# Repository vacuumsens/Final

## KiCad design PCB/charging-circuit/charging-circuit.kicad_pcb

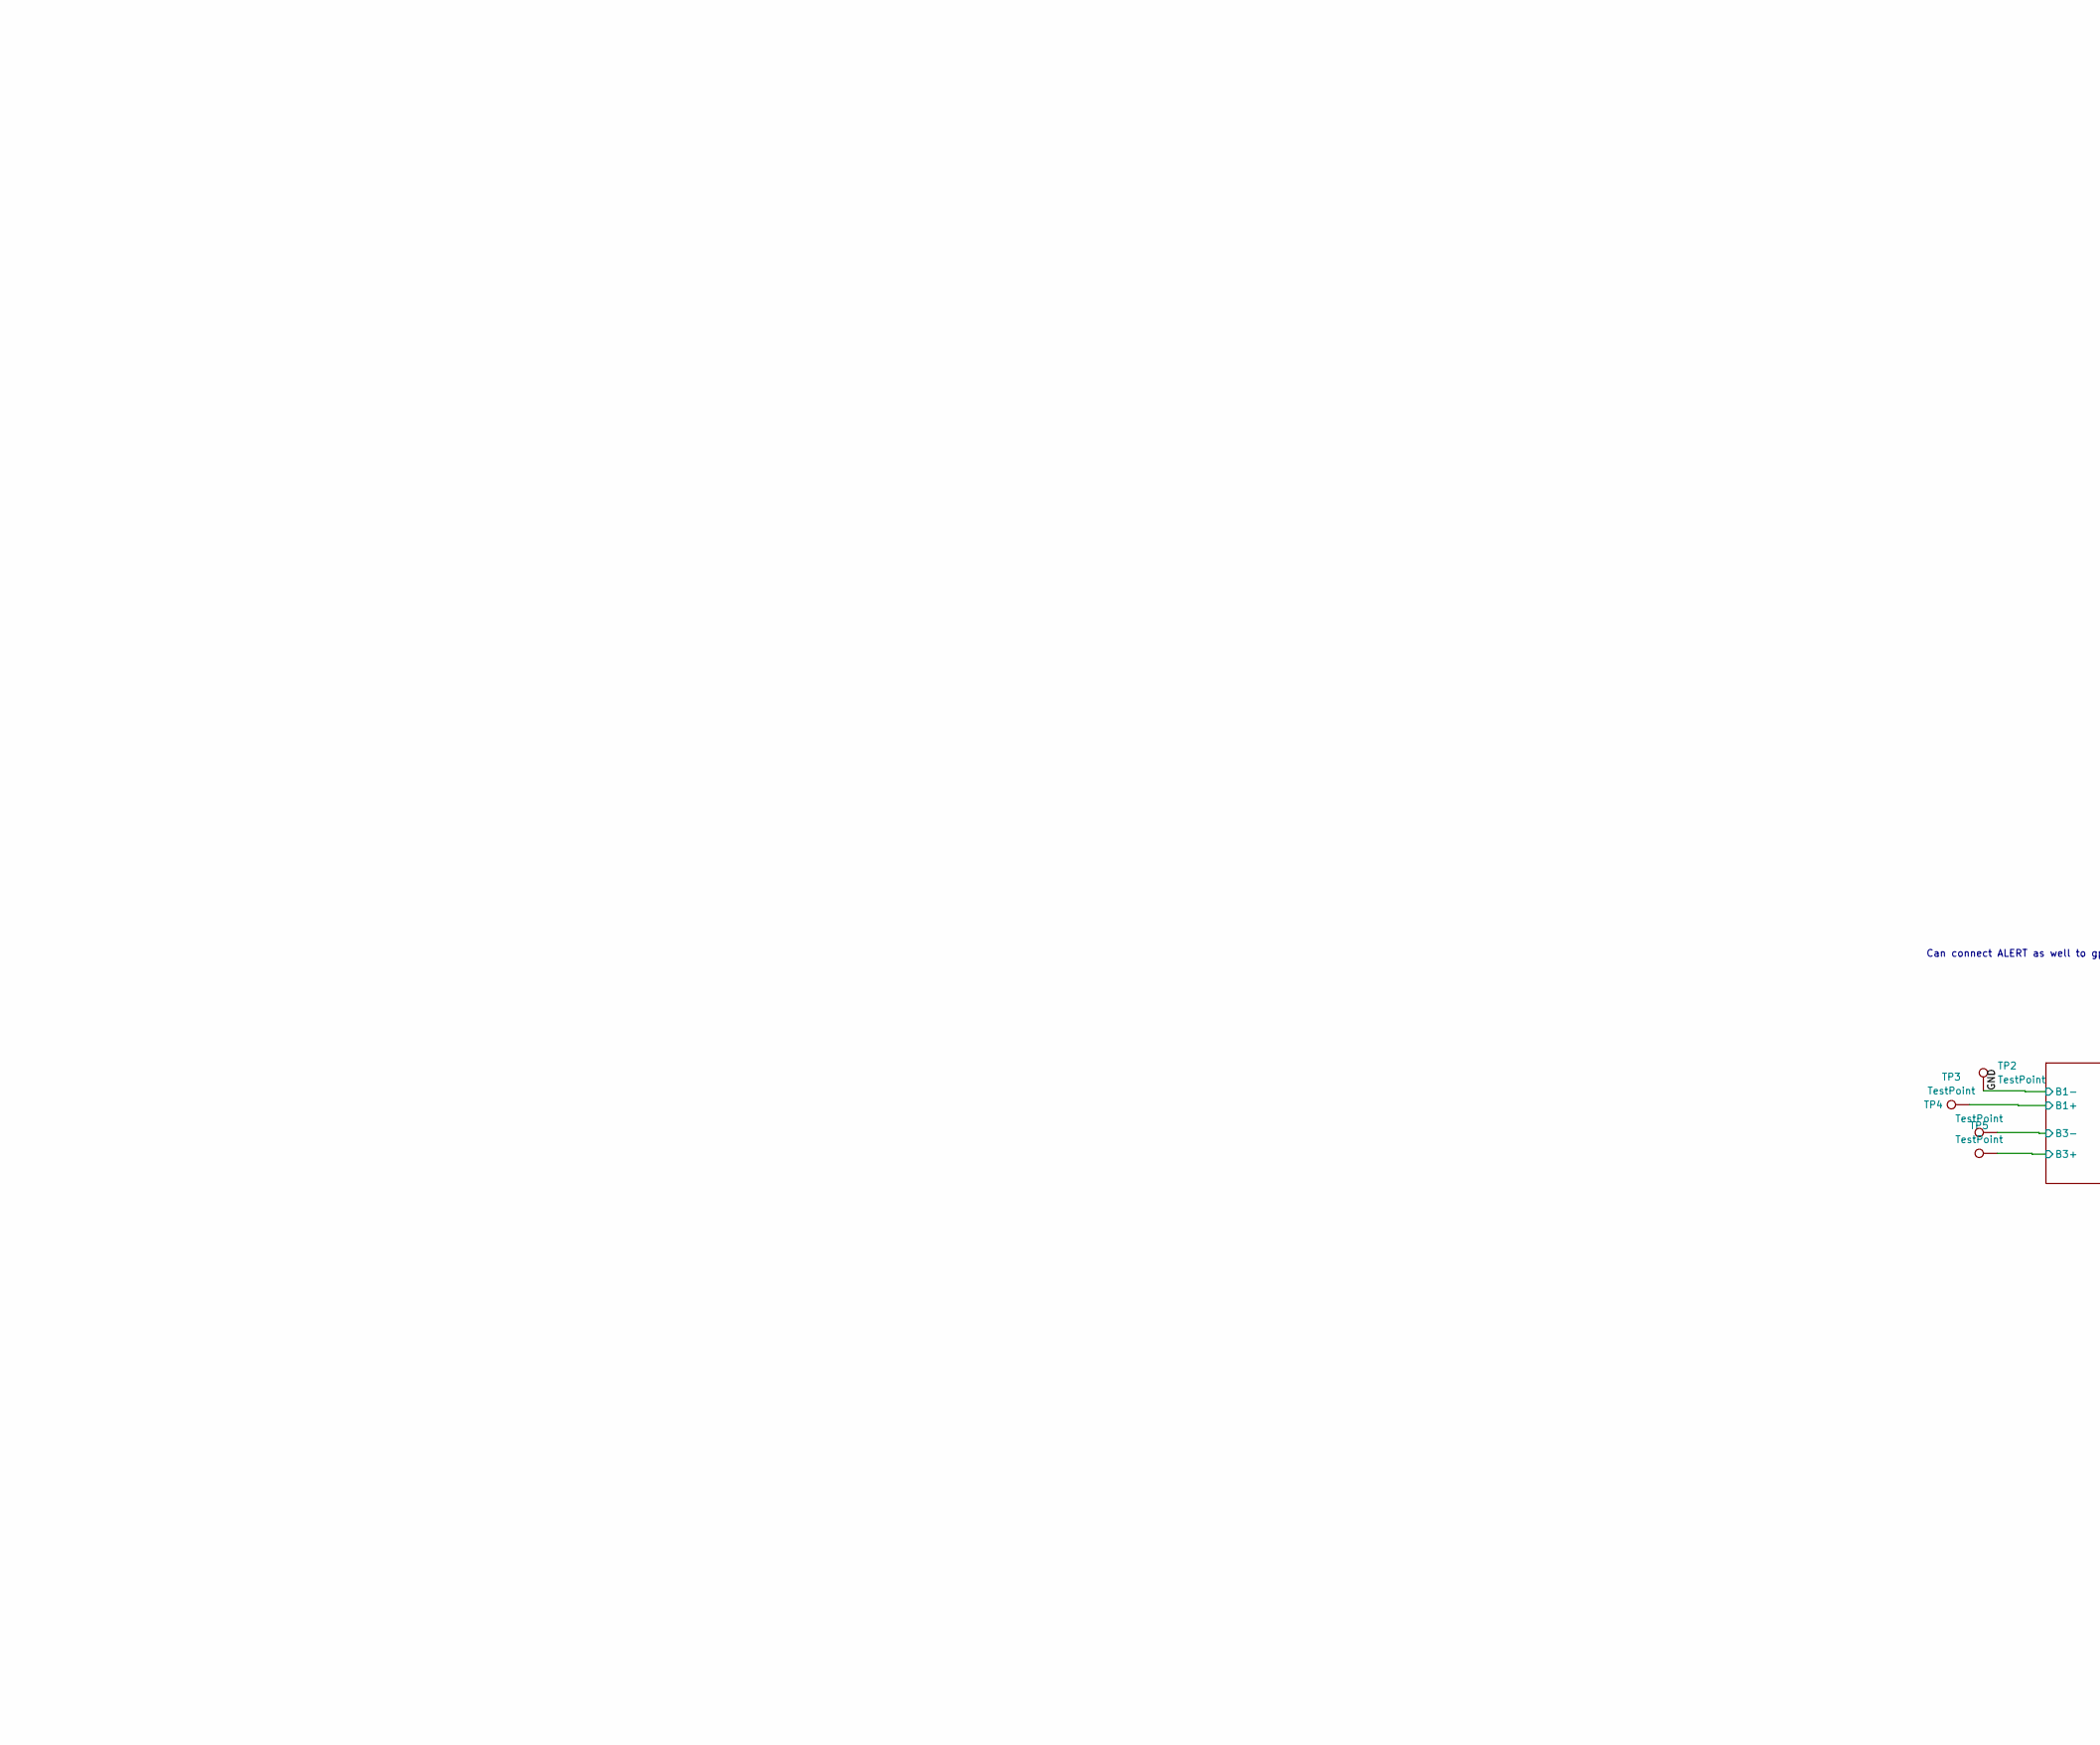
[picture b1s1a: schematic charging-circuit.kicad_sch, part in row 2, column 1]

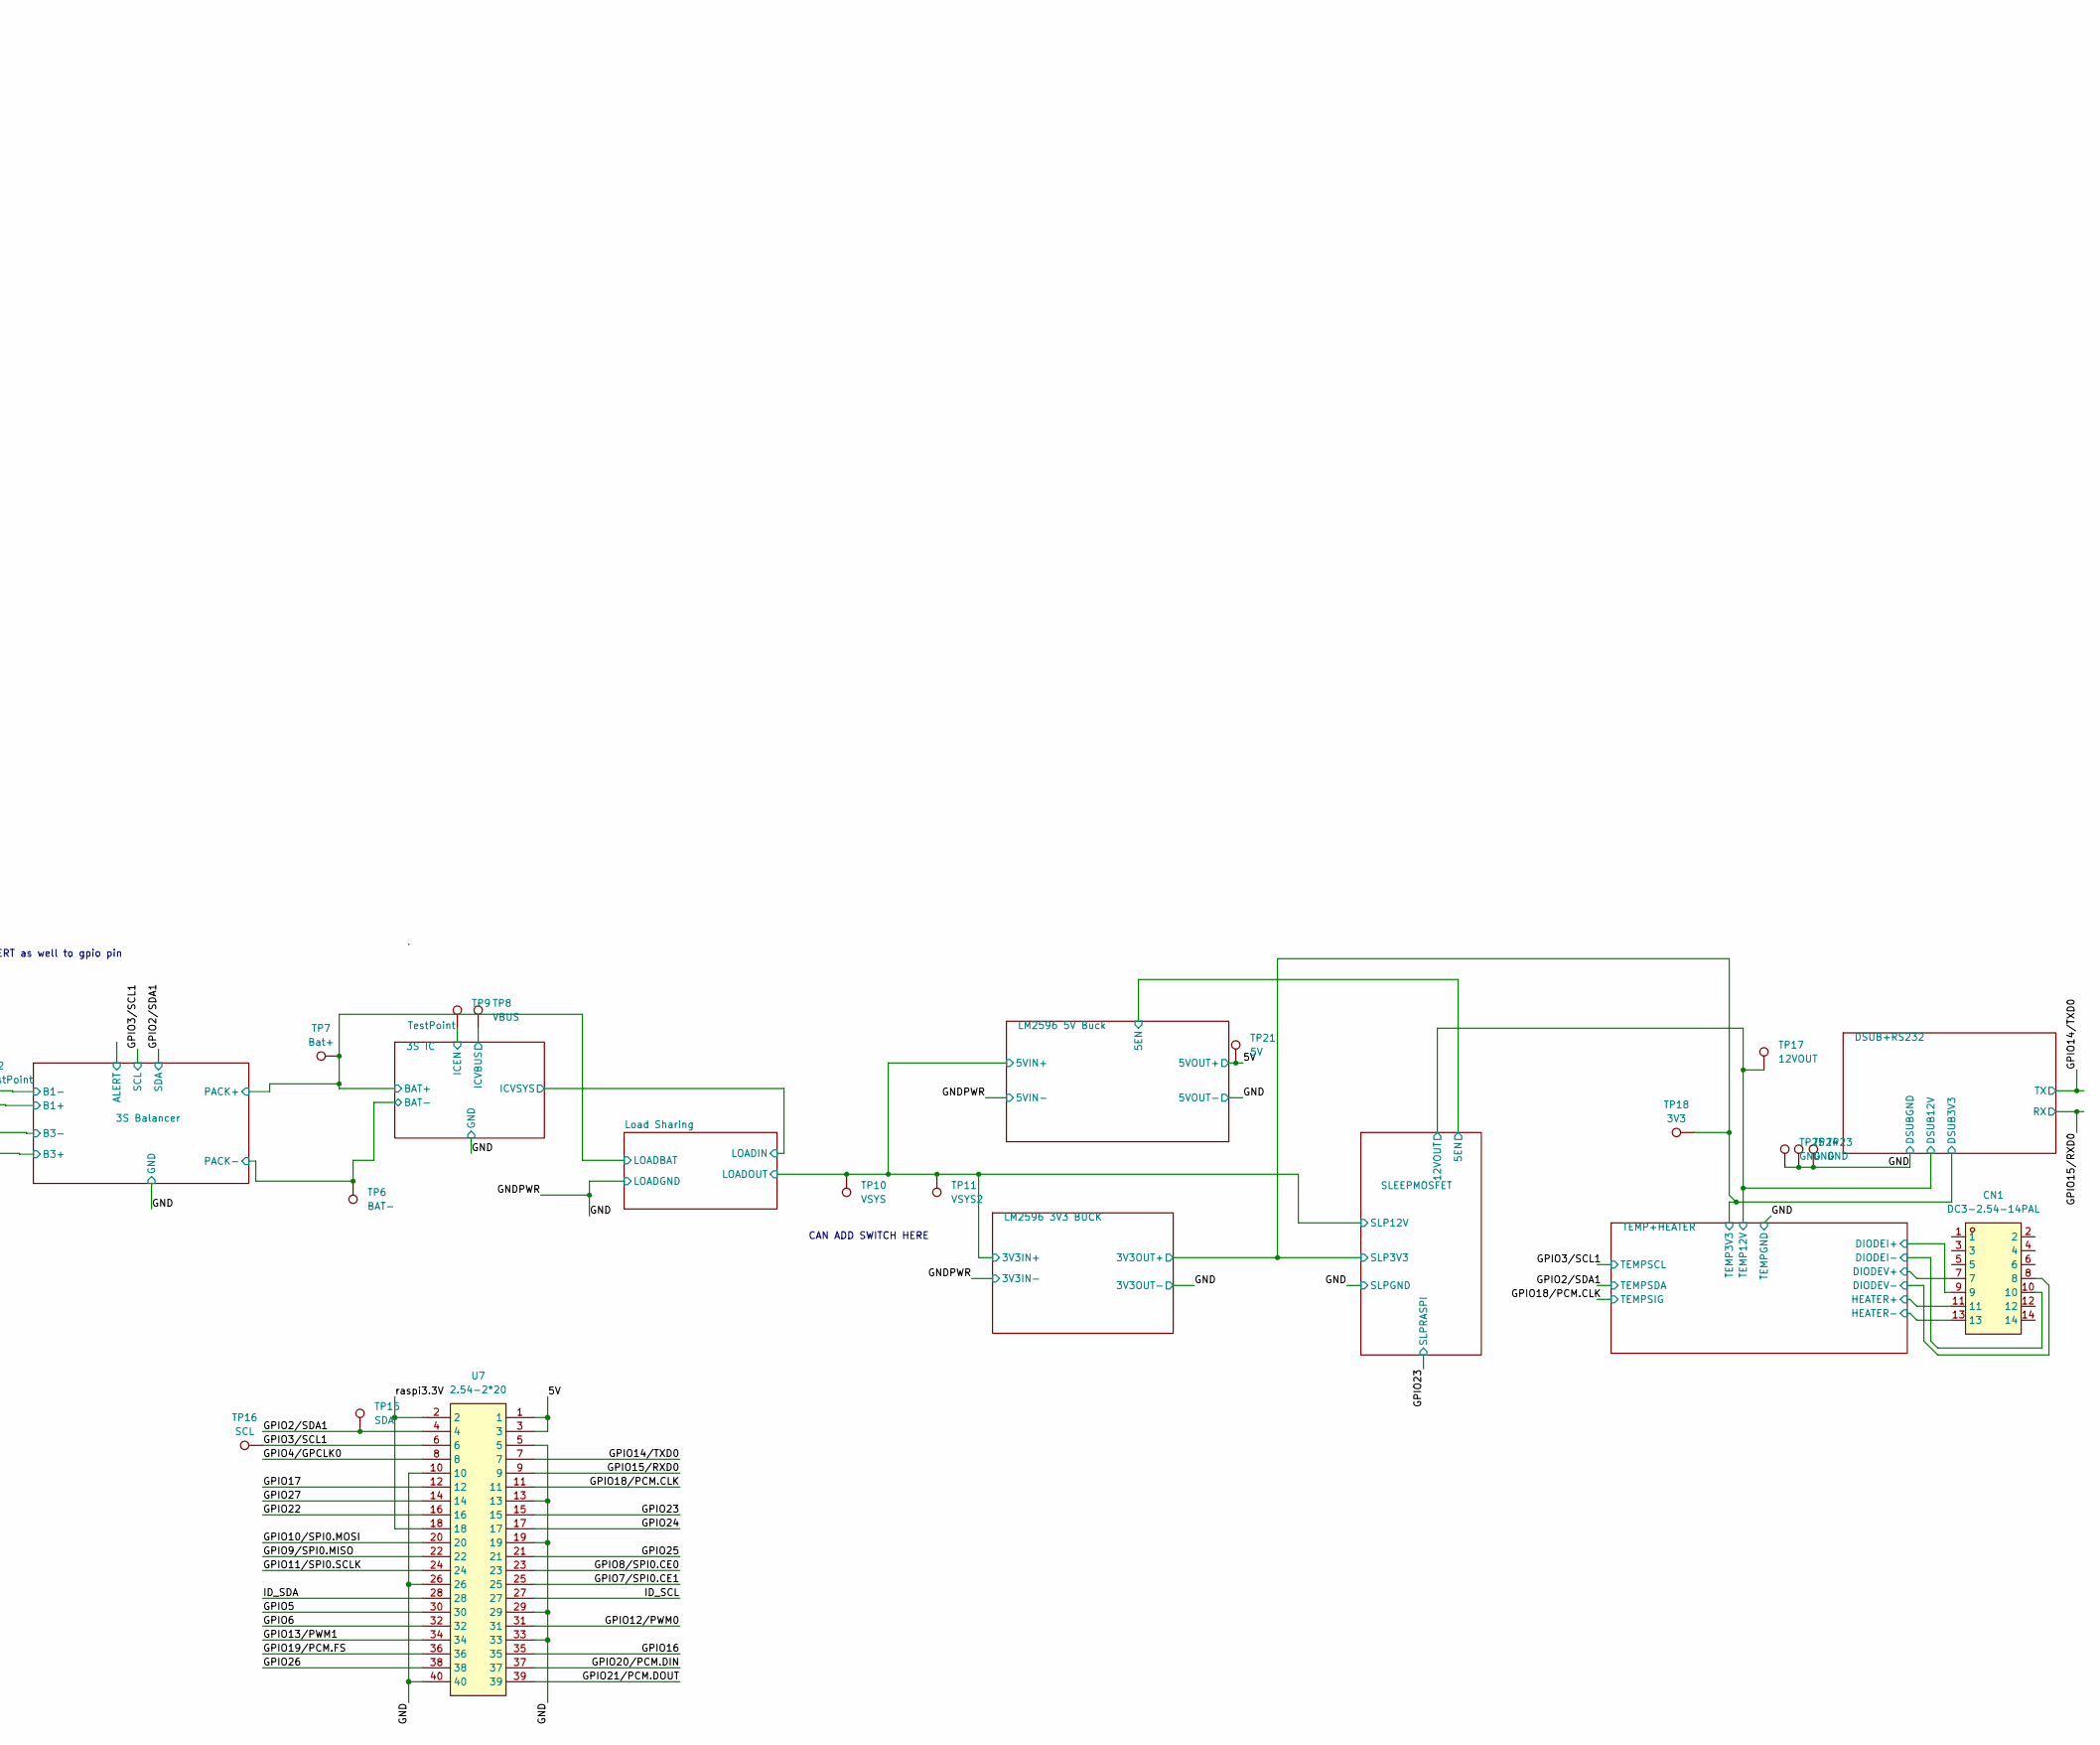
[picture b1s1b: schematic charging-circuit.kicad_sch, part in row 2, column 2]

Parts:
CN1: DC3-2.54-14PAL; IDC-TH_14P-P2.54_ZHOURI_DC3-2.54-14PAL; MPN DC3-2.54-14PAL; LCSC Part C5156673
TP2, TP3, TP4, TP5, TP9: TestPoint; PinHeader_1x01_P2.54mm_Vertical
TP6: BAT-; PinHeader_1x01_P2.54mm_Vertical
TP7: Bat+; PinHeader_1x01_P2.54mm_Vertical
TP8: VBUS; PinHeader_1x01_P2.54mm_Vertical
TP10: VSYS; PinHeader_1x01_P2.54mm_Vertical
TP11: VSYS2; PinHeader_1x01_P2.54mm_Vertical
TP15: SDA; PinHeader_1x01_P2.54mm_Vertical
TP16: SCL; PinHeader_1x01_P2.54mm_Vertical
TP17: 12VOUT; PinHeader_1x01_P2.54mm_Vertical
TP18: 3V3; PinHeader_1x01_P2.54mm_Vertical
TP21: 5V; PinHeader_1x01_P2.54mm_Vertical
TP23, TP24, TP25: GND; PinHeader_1x01_P2.54mm_Vertical
U7: 2.54-2*20; HDR-TH_40P-P2.54-V-F-R2-C20-S2.54; LCSC Part C2977589

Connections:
/3S Balancer/B1+: TP3.1 (1_1); also elsewhere on the board
/3S Balancer/B3-: TP4.1 (1_1); also elsewhere on the board
/3S IC/BAT+: TP5.1 (1_1), TP7.1 (1_1); also elsewhere on the board
/3S IC/ICEN: TP9.1 (1_1); also elsewhere on the board
/3S IC/ICVBUS: TP8.1 (1_1); also elsewhere on the board
/5V: TP21.1 (1_1), U7.1, U7.3; also elsewhere on the board
/DSUB+RS232/DSUB3.3V: CN1.9, TP18.1 (1_1); also elsewhere on the board
/DSUB+RS232/DSUB12V: TP17.1 (1_1); also elsewhere on the board
/GND: CN1.13, TP2.1 (1_1), TP6.1 (1_1), TP23.1 (1_1), TP24.1 (1_1), TP25.1 (1_1), U7.5, U7.10, U7.13, U7.19, U7.26, U7.29, U7.33, U7.40; also elsewhere on the board
/GPIO2/SDA1: TP15.1 (1_1), U7.4; also elsewhere on the board
/GPIO3/SCL1: TP16.1 (1_1), U7.6; also elsewhere on the board
/GPIO4/GPCLK0: U7.8
/GPIO5: U7.30
/GPIO6: U7.32
/GPIO7/SPI0.CE1: U7.25
/GPIO8/SPI0.CE0: U7.23
/GPIO9/SPI0.MISO: U7.22
/GPIO10/SPI0.MOSI: U7.20
/GPIO11/SPI0.SCLK: U7.24
/GPIO12/PWM0: U7.31
/GPIO13/PWM1: U7.34
/GPIO14/TXD0: U7.7; also elsewhere on the board
/GPIO15/RXD0: U7.9; also elsewhere on the board
/GPIO16: U7.35
/GPIO17: U7.12
/GPIO18/PCM.CLK: U7.11; also elsewhere on the board
/GPIO19/PCM.FS: U7.36
/GPIO20/PCM.DIN: U7.37
/GPIO21/PCM.DOUT: U7.39
/GPIO22: U7.16
/GPIO23: U7.15; also elsewhere on the board
/GPIO24: U7.17
/GPIO25: U7.21
/GPIO26: U7.38
/GPIO27: U7.14
/ID_SCL: U7.27
/ID_SDA: U7.28
/LM2596 3V3 BUCK/LM2596_VIN: TP10.1 (1_1), TP11.1 (1_1); also elsewhere on the board
/TEMP+HEATER/A0: CN1.8; also elsewhere on the board
/TEMP+HEATER/A1: CN1.7; also elsewhere on the board
/TEMP+HEATER/DIODEI-: CN1.10; also elsewhere on the board
/TEMP+HEATER/HEATER+: CN1.11; also elsewhere on the board
/raspi3.3V: U7.2, U7.18

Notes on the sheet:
Can connect ALERT as well to gpio pin
CAN ADD SWITCH HERE

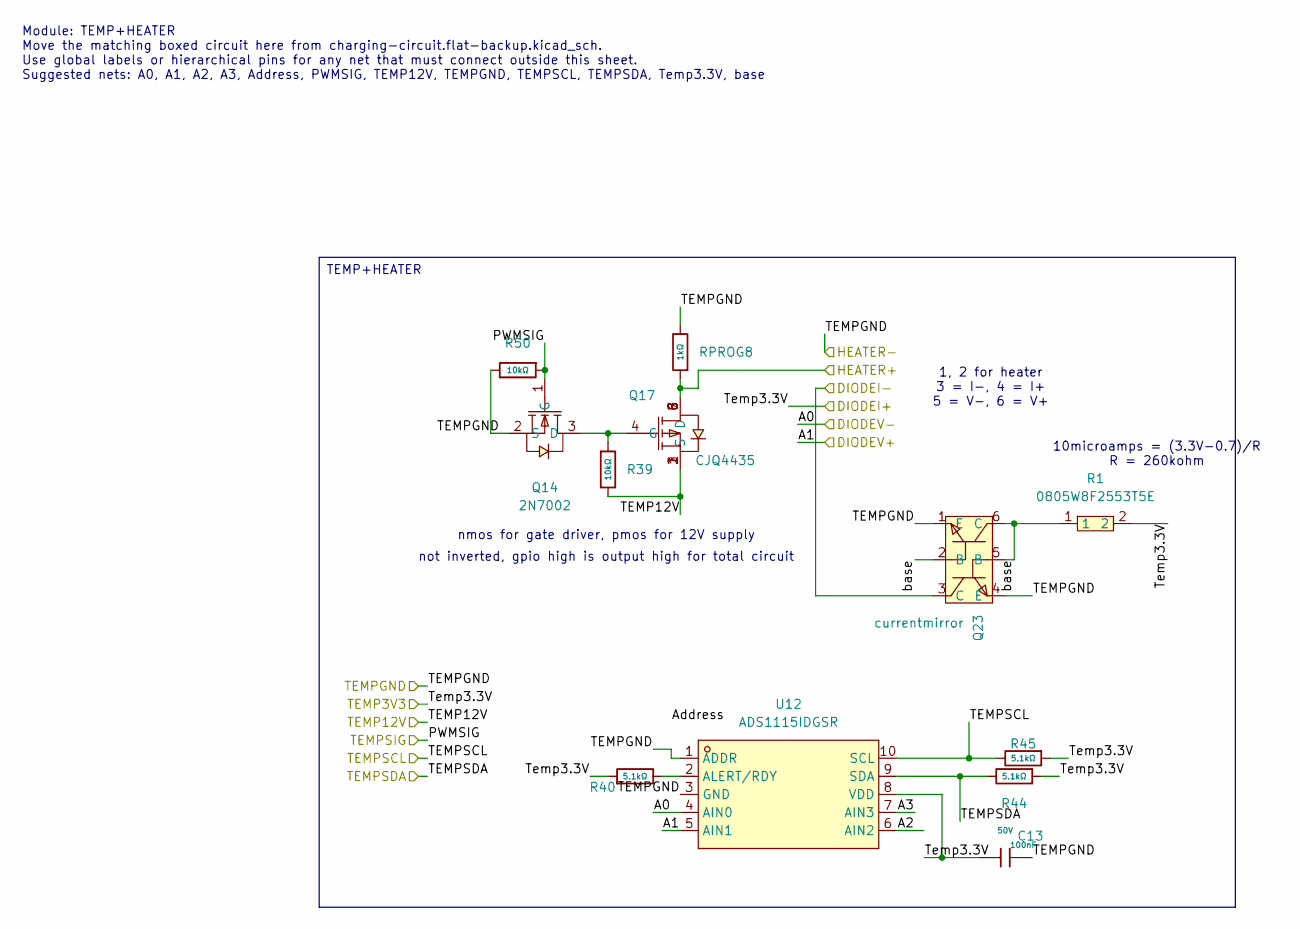
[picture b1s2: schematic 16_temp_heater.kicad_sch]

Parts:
C13: 100nF; C_0603; Voltage Rated 50V; Tolerance ±10%; Part CC0603KRX7R9BB104; LCSC C14663
Q14: 2N7002; SOT-23-3_L2.9-W1.3-P1.90-LS2.4-BR; LCSC Part C8545
Q17: CJQ4435; SOP-8_L5.0-W4.0-P1.27-LS6.2-BL; LCSC Part C114076
Q23: currentmirror; SOT-363-6_L2.2-W1.3-P0.65-LS2.1-BL; LCSC Part C41375126
R1: 0805W8F2553T5E; R0805; MPN 0805W8F2553T5E; LCSC Part C17578
R39, R50: 10kΩ; R_0603; Overload Voltage (Max) 75V; Tolerance ±1%; Part 0603WAF1002T5E; LCSC C25804
R40, R44, R45: 5.1kΩ; R_0603; Overload Voltage (Max) 75V; Tolerance ±1%; Part 0603WAF5101T5E; LCSC C23186
RPROG8: 1kΩ; R_0603; Overload Voltage (Max) 75V; Tolerance ±1%; Part 0603WAF1001T5E; LCSC C21190
U12: ADS1115IDGSR; MSOP-10_L3.0-W3.0-P0.50-LS5.0-BL; LCSC Part C37593

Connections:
/DSUB+RS232/DSUB3.3V: C13.1, R1.2, R40.1, R44.1, R45.1, U12.8 (VDD); also elsewhere on the board
/DSUB+RS232/DSUB12V: Q17.1 (S), Q17.2 (S), Q17.3 (S), R39.2; also elsewhere on the board
/GND: C13.2, Q14.2 (S), Q23.1 (E), Q23.4 (E), R50.2, RPROG8.2, U12.1 (ADDR), U12.3 (GND); also elsewhere on the board
/GPIO2/SDA1: R44.2, U12.9 (SDA); also elsewhere on the board
/GPIO3/SCL1: R45.2, U12.10 (SCL); also elsewhere on the board
/GPIO18/PCM.CLK: Q14.1 (G), R50.1; also elsewhere on the board
/TEMP+HEATER/A0: U12.4 (AIN0); also elsewhere on the board
/TEMP+HEATER/A1: U12.5 (AIN1); also elsewhere on the board
/TEMP+HEATER/A2: U12.6 (AIN2)
/TEMP+HEATER/A3: U12.7 (AIN3)
/TEMP+HEATER/DIODEI-: Q23.3 (C); also elsewhere on the board
/TEMP+HEATER/HEATER+: Q17.5 (D), Q17.6 (D), Q17.7 (D), Q17.8 (D), RPROG8.1; also elsewhere on the board
/TEMP+HEATER/base: Q23.2 (B), Q23.5 (B), Q23.6 (C), R1.1
unnamed: Q14.3 (D), Q17.4 (G), R39.1
unnamed: R40.2, U12.2 (ALERT/RDY)

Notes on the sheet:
1, 2 for heater 3 = I-, 4 = I+ 5 = V-, 6 = V+
10microamps = (3.3V-0.7)/R R = 260kohm
not inverted, gpio high is output high for total circuit
Module: TEMP+HEATER Move the matching boxed circuit here from charging-circuit.flat-backup.kicad_sch. Use global labels or hierarchical pins for any net that must connect outside this sheet. Suggested nets: A0, A1, A2, A3, Address, PWMSIG, TEMP12V, TEMPGND, TEMPSCL, TEMPSDA, Temp3.3V, base
nmos for gate driver, pmos for 12V supply
TEMP+HEATER

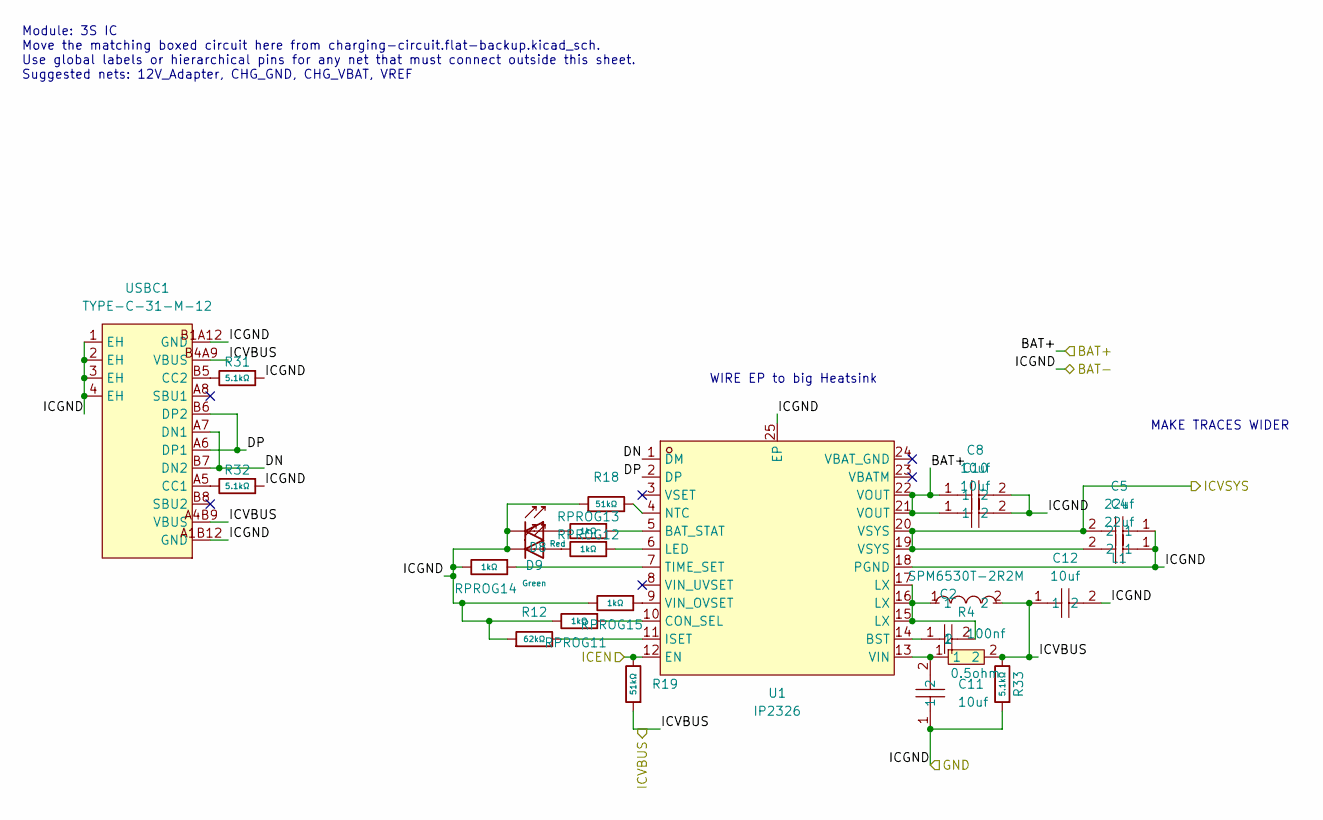
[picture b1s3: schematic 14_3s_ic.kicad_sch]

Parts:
C2: 100nf; C0805; MPN CL21B104KBCNNNC; LCSC Part C1711
C4, C5: 22uf; C0805; LCSC Part C45783
C8, C10, C11, C12: 10uf; C0805; MPN GRM21BR61E106KA73L; LCSC Part C84416
D8: Red; D_0805; Forward Voltage (VF) 1.6V~2.6V; Part NCD0805R1; LCSC C84256
D9: Green; D_0805; Part KT-0805G; LCSC C2297
L1: SPM6530T-2R2M; IND-SMD_L7.1-W6.5-P5.60; MPN SPM6530T-2R2M; LCSC Part C76855
R4: 0.5ohm; R1206; MPN 1206W4F500LT5E; LCSC Part C25340
R12: 62kΩ; R_0805; Overload Voltage (Max) 150V; Tolerance ±1%; Part 0805W8F6202T5E; LCSC C17783
R18, R19: 51kΩ; R_0805; Overload Voltage (Max) 150V; Tolerance ±1%; Part 0805W8F5102T5E; LCSC C17737
R31, R32, R33: 5.1kΩ; R_0603; Overload Voltage (Max) 75V; Tolerance ±1%; Part 0603WAF5101T5E; LCSC C23186
RPROG11, RPROG12, RPROG13, RPROG14, RPROG15: 1kΩ; R_0603; Overload Voltage (Max) 75V; Tolerance ±1%; Part 0603WAF1001T5E; LCSC C21190
U1: IP2326; VQFN-24_L4.0-W4.0-P0.50-BL-EP2.5; MPN IP2326; LCSC Part C2832094
USBC1: TYPE-C-31-M-12; USB-C_SMD-TYPE-C-31-M-12_1; LCSC Part C165948

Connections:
/3S IC/BAT+: C8.1, C10.1, U1.21 (VOUT), U1.22 (VOUT); also elsewhere on the board
/3S IC/DN: U1.1 (DM), USBC1.A7 (DN1), USBC1.B7 (DN2)
/3S IC/DP: U1.2 (DP), USBC1.A6 (DP1), USBC1.B6 (DP2)
/3S IC/ICEN: R19.2, U1.12 (EN); also elsewhere on the board
/3S IC/ICVBUS: C12.1, L1.2, R4.2, R19.1, R33.2, USBC1.A4B9 (VBUS), USBC1.B4A9 (VBUS); also elsewhere on the board
/GND: C4.1, C5.1, C8.2, C10.2, C11.1, C12.2, D8.1, D9.1, R12.1, R18.1, R31.1, R32.1, R33.1, RPROG11.2, RPROG14.2, RPROG15.2, U1.18 (PGND), U1.25 (EP), USBC1.1 (EH), USBC1.2 (EH), USBC1.3 (EH), USBC1.4 (EH), USBC1.A1B12 (GND), USBC1.B1A12 (GND); also elsewhere on the board
/Load Sharing/VSYS: C4.2, C5.2, U1.19 (VSYS), U1.20 (VSYS); also elsewhere on the board
unnamed: C2.2, L1.1, U1.15 (LX), U1.16 (LX), U1.17 (LX)
unnamed: D8.2, RPROG13.2
unnamed: D9.2, RPROG12.2
unnamed: RPROG13.1, U1.5 (BAT_STAT)
unnamed: C2.1, U1.14 (BST)
unnamed: RPROG11.1, U1.10 (CON_SEL)
unnamed: R12.2, U1.11 (ISET)
unnamed: RPROG12.1, U1.6 (LED)
unnamed: R18.2, U1.4 (NTC)
unnamed: RPROG14.1, U1.7 (TIME_SET)
unnamed: C11.2, R4.1, U1.13 (VIN)
unnamed: RPROG15.1, U1.9 (VIN_OVSET)
unnamed: R32.2, USBC1.A5 (CC1)
unnamed: R31.2, USBC1.B5 (CC2)

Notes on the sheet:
Module: 3S IC Move the matching boxed circuit here from charging-circuit.flat-backup.kicad_sch. Use global labels or hierarchical pins for any net that must connect outside this sheet. Suggested nets: 12V_Adapter, CHG_GND, CHG_VBAT, VREF
WIRE EP to big Heatsink
MAKE TRACES WIDER

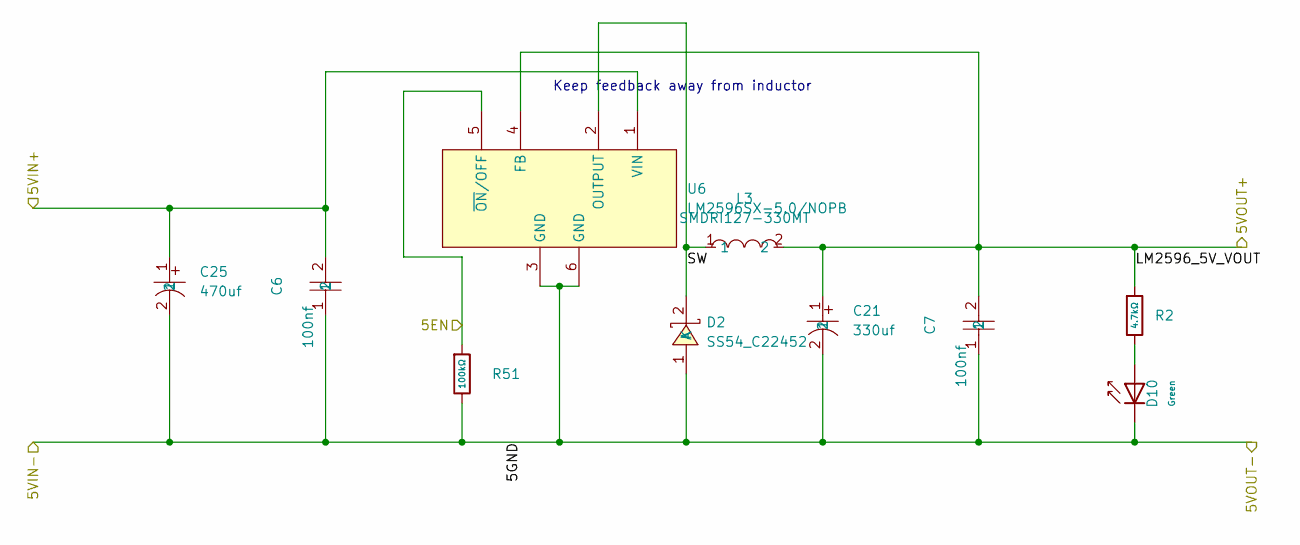
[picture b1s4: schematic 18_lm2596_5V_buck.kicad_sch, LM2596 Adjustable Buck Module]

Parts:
C6, C7: 100nf; C0805; MPN CL21B104KBCNNNC; LCSC Part C1711
C21: 330uf; CAP-SMD_BD10.0-L10.3-W10.3-FD; MPN RVT1V331M1010; LCSC Part C19606
C25: 470uf; CAP-SMD_BD10.0-L10.3-W10.3-LS11.0-FD; MPN RVT1E471M1010; LCSC Part C3351
D2: SS54_C22452; SMA_L4.4-W2.8-LS5.4-R-RD; MPN SS54; LCSC Part C22452
D10: Green; D_0805; Part KT-0805G; LCSC C2297
L3: SMDRI127-330MT; IND-SMD_L12.3-W12.3; MPN SMDRI127-330MT; LCSC Part C9400
R2: 4.7kΩ; R_0805; Overload Voltage (Max) 150V; Tolerance ±1%; Part 0805W8F4701T5E; LCSC C17673
R51: 100kΩ; R_0603; Overload Voltage (Max) 75V; Tolerance ±1%; Part 0603WAF1003T5E; LCSC C25803
U6: LM2596SX-5.0/NOPB; TO-263-5_L10.2-W8.9-P1.70-TL; MPN LM2596SX-5.0/NOPB; LCSC Part C10002

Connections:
/5V: C7.2, C21.1, L3.2, R2.1, U6.4 (FB); also elsewhere on the board
/GND: C6.1, C7.1, C21.2, C25.2, D2.1 (A), D10.1, R51.2, U6.3 (GND), U6.6 (GND); also elsewhere on the board
/LM2596 3V3 BUCK/LM2596_VIN: C6.2, C25.1, U6.1 (VIN); also elsewhere on the board
/LM2596 5V Buck/SW: D2.2 (K), L3.1, U6.2 (OUTPUT)
/SLEEPMOSFET/5EN: R51.1, U6.5 (~ON/OFF); also elsewhere on the board
unnamed: D10.2, R2.2

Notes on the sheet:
Keep feedback away from inductor

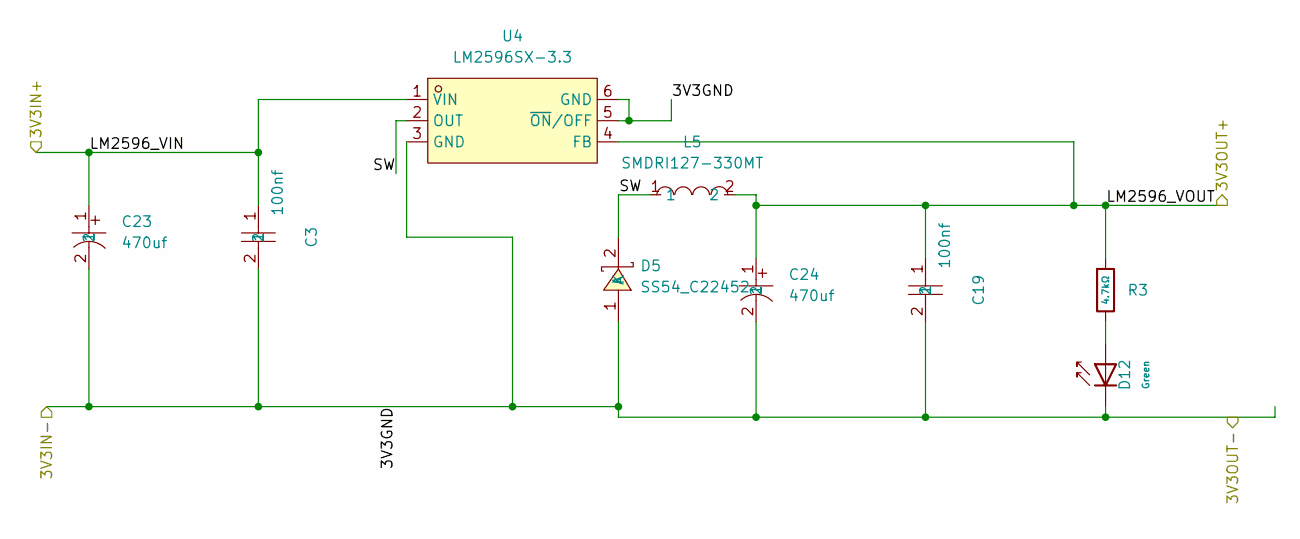
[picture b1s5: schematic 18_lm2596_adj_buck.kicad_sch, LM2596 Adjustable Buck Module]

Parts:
C3, C19: 100nf; C0805; MPN CL21B104KBCNNNC; LCSC Part C1711
C23, C24: 470uf; CAP-SMD_BD10.0-L10.3-W10.3-LS11.0-FD; MPN RVT1E471M1010; LCSC Part C3351
D5: SS54_C22452; SMA_L4.4-W2.8-LS5.4-R-RD; MPN SS54; LCSC Part C22452
D12: Green; D_0805; Part KT-0805G; LCSC C2297
L5: SMDRI127-330MT; IND-SMD_L12.3-W12.3; MPN SMDRI127-330MT; LCSC Part C9400
R3: 4.7kΩ; R_0805; Overload Voltage (Max) 150V; Tolerance ±1%; Part 0805W8F4701T5E; LCSC C17673
U4: LM2596SX-3.3; TO-263-5_L10.2-W8.6-P1.70-LS14.4-TL; MPN LM2596SX-3.3; LCSC Part C5186052

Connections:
/DSUB+RS232/DSUB3.3V: C19.1, C24.1, L5.2, R3.1, U4.4 (FB); also elsewhere on the board
/GND: C3.2, C19.2, C23.2, C24.2, D5.1 (A), D12.1, U4.3 (GND), U4.5 (~ON/OFF), U4.6 (GND); also elsewhere on the board
/LM2596 3V3 BUCK/LM2596_VIN: C3.1, C23.1, U4.1 (VIN); also elsewhere on the board
/LM2596 3V3 BUCK/SW: D5.2 (K), L5.1, U4.2 (OUT)
unnamed: D12.2, R3.2

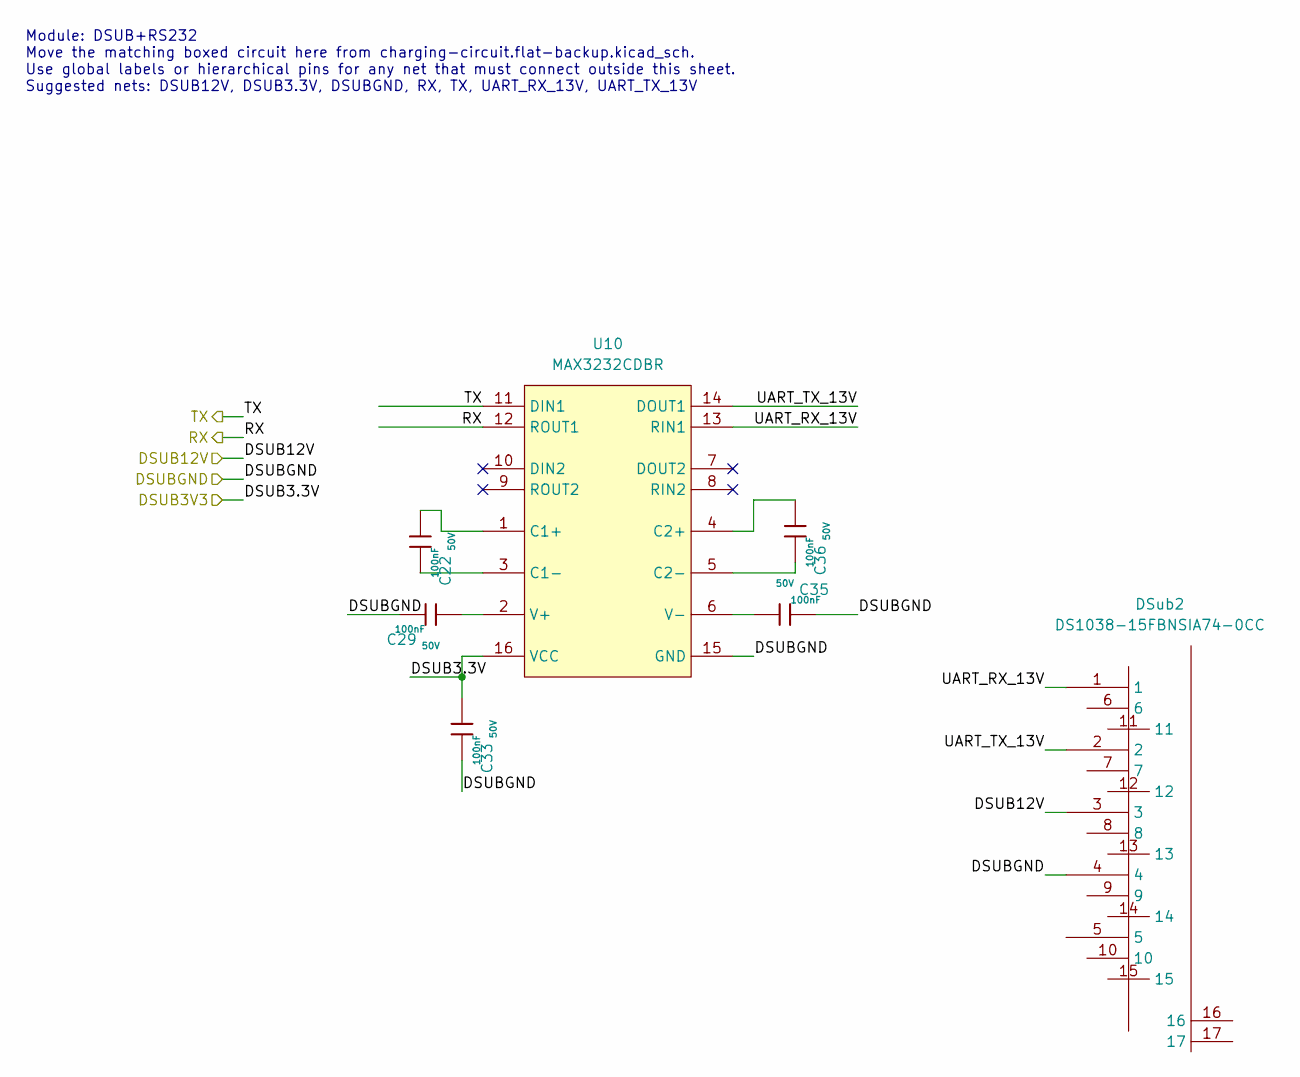
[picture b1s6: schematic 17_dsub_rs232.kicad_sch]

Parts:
C22, C29, C33, C35, C36: 100nF; C_0603; Voltage Rated 50V; Tolerance ±10%; Part CC0603KRX7R9BB104; LCSC C14663
DSub2: DS1038-15FBNSIA74-0CC; DSUB-TH_DS1038-15FBNSIA74-0CC; LCSC Part C75754
U10: MAX3232CDBR; SSOP-16_L6.2-W5.3-P0.65-LS7.8-BL; LCSC Part C7257

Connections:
/DSUB+RS232/DSUB3.3V: C33.1, U10.16 (VCC); also elsewhere on the board
/DSUB+RS232/DSUB12V: DSub2.3; also elsewhere on the board
/DSUB+RS232/UART_RX_13V: DSub2.1, U10.13 (RIN1)
/DSUB+RS232/UART_TX_13V: DSub2.2, U10.14 (DOUT1)
/GND: C29.2, C33.2, C35.2, DSub2.4, U10.15 (GND); also elsewhere on the board
/GPIO14/TXD0: U10.11 (DIN1); also elsewhere on the board
/GPIO15/RXD0: U10.12 (ROUT1); also elsewhere on the board
unnamed: C22.1, U10.1 (C1+)
unnamed: C22.2, U10.3 (C1-)
unnamed: C36.1, U10.4 (C2+)
unnamed: C36.2, U10.5 (C2-)
unnamed: C29.1, U10.2 (V+)
unnamed: C35.1, U10.6 (V-)

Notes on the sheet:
Module: DSUB+RS232 Move the matching boxed circuit here from charging-circuit.flat-backup.kicad_sch. Use global labels or hierarchical pins for any net that must connect outside this sheet. Suggested nets: DSUB12V, DSUB3.3V, DSUBGND, RX, TX, UART_RX_13V, UART_TX_13V

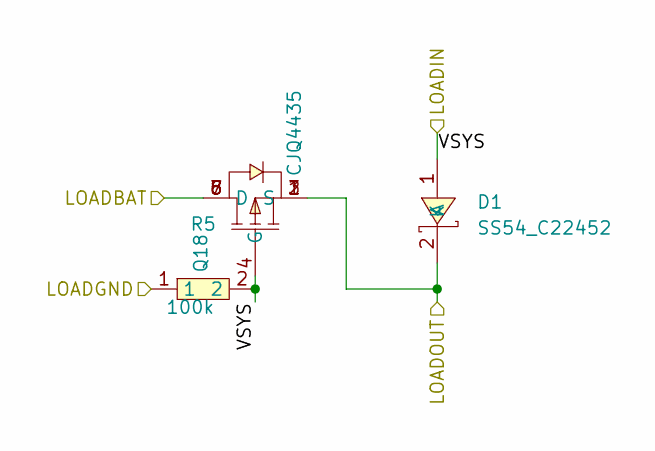
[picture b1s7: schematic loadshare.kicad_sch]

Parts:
D1: SS54_C22452; SMA_L4.4-W2.8-LS5.4-R-RD; MPN SS54; LCSC Part C22452
Q18: CJQ4435; SOP-8_L5.0-W4.0-P1.27-LS6.2-BL; LCSC Part C114076
R5: 100k; R0805; MPN 0805W8J0104T5E; LCSC Part C25611

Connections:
/3S IC/BAT+: Q18.5 (D), Q18.6 (D), Q18.7 (D), Q18.8 (D); also elsewhere on the board
/GND: R5.1; also elsewhere on the board
/LM2596 3V3 BUCK/LM2596_VIN: D1.2 (K), Q18.1 (S), Q18.2 (S), Q18.3 (S); also elsewhere on the board
/Load Sharing/VSYS: D1.1 (A), Q18.4 (G), R5.2; also elsewhere on the board
